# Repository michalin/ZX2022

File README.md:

# ZX 2022
Yet another homebuilt Z80 Computer, but this one works without any FPGAs or Microcontrollers, but components that were available at the time when the Z80 processor was state of the art. It can run historic CP/M programs like Multiplan, Wordstar and MBasic, as well as some games. This is a reminiscense to the Sinclair ZX81 computer. 
In contrast to its predecessor, the ZX2020, this one uses a 32 kilobyte EE Prom to reliably store the CP/M BDOS and BIOS. Furthermore a PS/2, or  PS/2 compatible USB keyboard can be connected. With an optional TMS99x8 based video card, a  TV or monitor can also be used. This repository contains gerber files for both the ZX2022 and the video  card. So it can now be easily replicated.

## Features
- Zilog Z80 processor @6MHz, higher clock rates might also work.
- 128 Kilobytes of static RAM, can be switched in banks of 32k
- 32 Kilobytes of EEprom
- 2 Serial UART ports 187.5 kBaud (Clock freqency/32):
  - Terminal emulation, (Putty works best)
  - File transfer. Files in a special folder on the PC show up as drive B>
- EEprom provides 15 Kilobytes of file memory (drive A>). CP/M executables are started automatically after reset or power on
- IDE (PATA) interface. Provides 4x16 Kilobyte organized as drives C>..F>
- CP/M 3.0
- 64-Pin connector for up to 6 Extension modules
- Optional graphics card with TMS99x8. 
    - 256x192 pixels and 15 colors
    - 32 Sprites (8x8, 16x16 or 32x32 upscaled)
    - NTSC (TMS9918) or PAL (TMS9928)
- Supports PS/2 or PS/2 compatible USB keyboards. New USB keyboards or wireless keyboards may NOT work.
- Now programmable in C using SDCC (Small Device C Compiler)

## To build the ZX 2022, do the following
- Wire the parts on a breadboard or prototype board according to the schematic. 
- OR: Make or order a PCB based on the gerber files `./Schematic/Mainboard/gerber-main.zip` (Recommended)
- Load the Arduino Sketch `loader/loader.ino` into an Arduino Mega
- Plug the Arduino Mega on the Bus connector, where it is marked on the silkscreen
- Connect the TxB and RxB pins of the DART with Pin 0 (TX0) and 1 (RX0) of your Arduino Mega
- Start a serial terminal emulation, for example "Putty", set 187500 Baud, 8 Bit, 1 Stopbit, no parity
- On Windows, run the tool `bin/loader.exe`. Click on "ROM Image" and select the file `CPM/rom.img`
- When a welcome message and the CP/M prompt "B>" appears on your terminal emulation, the ZX2020 is ready to use. If you have a PATA compatible hard drive connected, you need to format it under CP/M with the "mkdsk.com" tool before you can use it. Note that all data on the disk will be lost. 

## Using The Serial Disk Drive
Connect RX0 of the Arduino with TxB and TX0 with RxB of the ZX2022. 
It is not necessary to plug the Arduino into the pin header. Instead of an Arduino, a USB to serial converter may be used here as well. Select the serial port in the drop down menu and check the "Connect" check box to establish the serial connection. After a reset, the serial disk drive can be accessed as drive B>.

The folder [CPM/serdisk](./CPM/serdisk/) contains the CP/M programs in up to 16 user folders numbered from 0 to 15. If any of these files have changed, click the "Reload" Button to apply the changes. To access the files from CP/M, type `B`, followed by the user number 1-15 and a colon. For example `B5:` gives access to the files under [CPM/serdisk/5](./CPM/serdisk/5)

## Connecting a Hard Drive
IDE (PATA) hard drives can be connected through a 40-Pin connector. I recommend using a CompactFlash with a CF to IDE adapter. Best suitable are adapters that support power supply over pin 20 like this one: [https://amzn.to/3SFdIag](https://amzn.to/3SFdIag). call ´mkdsk.com´ on the serial disk drive B> to format the drive.

## The Autostart Feature
Clicking the `File` button in the loader app uploads an executable CP/M file (*.com) that is executed after each power-on or reboot. The loader app detects when there is a new version of this "autostart program" and restarts the ZX2022 with this new version. This function is particularly useful for writing new software.

## Connecting a PS/2 Keyboard
Connect a PS/2 Keyboard like shown below:

## Connecting a USB Keyboard
USB Keyboards can also be connected if they support the PS/2 protocol. Most older keyboards do so, but newer or wireless keyboards often don't. These will not work.
I recommend to make an adapter cable from an USB extension cable as shown below:

## Changing the keyboard layout 
This is only necessary with PS/2 or USB keyboards. With terminal connections, the settings of the Windows-OS apply.
To change the keyboard layout, set the `KBLAYOUT` variable in the file [CPM/SYSCFG.LIB](./CPM/SYSCFG.LIB) either to `DE` or `EN` (default)
and [rebuild the CP/M rom image](CPM/README.md).

## Using With the TMS9918 Video Card
You find the schematic and gerber files in [Schematic/Video/](./Schematic/Video/). Set a jumper or solder a bridge at the position `IO2` on the pin header J3. This configures the card for IO addresses starting at 20h. This setting must match the `p$vdp` constant in [CPM/SYSCFG.LIB](./CPM/SYSCFG.LIB)

The TMS9918 can only display 40 columns, while terminals display 80 columns. This CP/M version is built for 80 columns, but it can be changed to 40 columns. To do this, open the file [gencpm.dat](./CPM/gencpm.dat), change the constant `PAGWID` to 28 (Which is 40 in hex) and [rebuild the CP/M rom image](CPM/README.md).

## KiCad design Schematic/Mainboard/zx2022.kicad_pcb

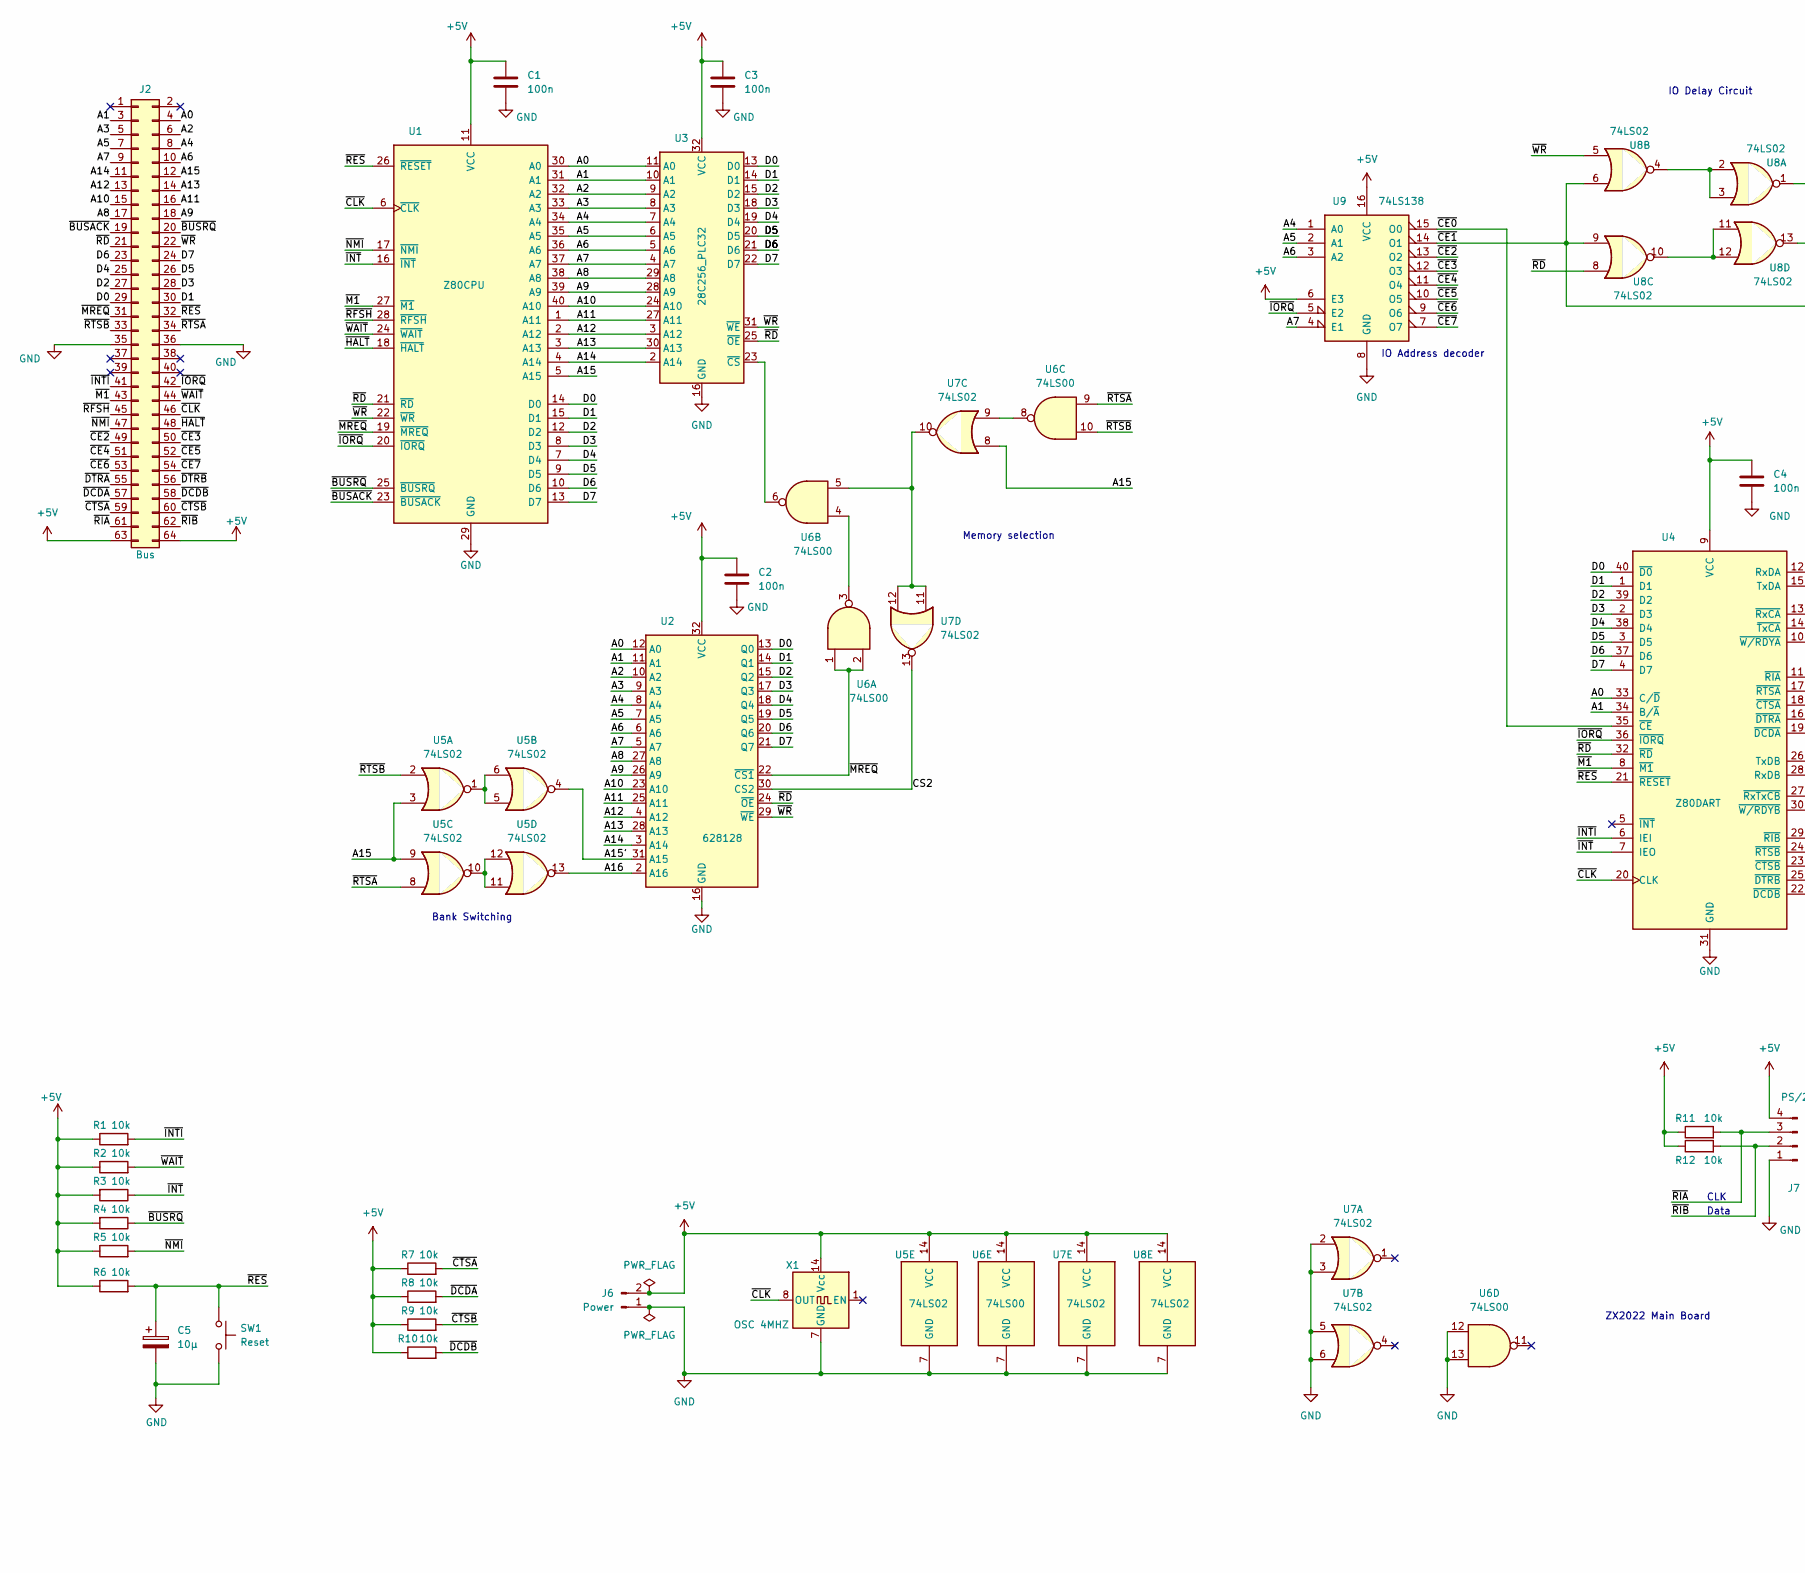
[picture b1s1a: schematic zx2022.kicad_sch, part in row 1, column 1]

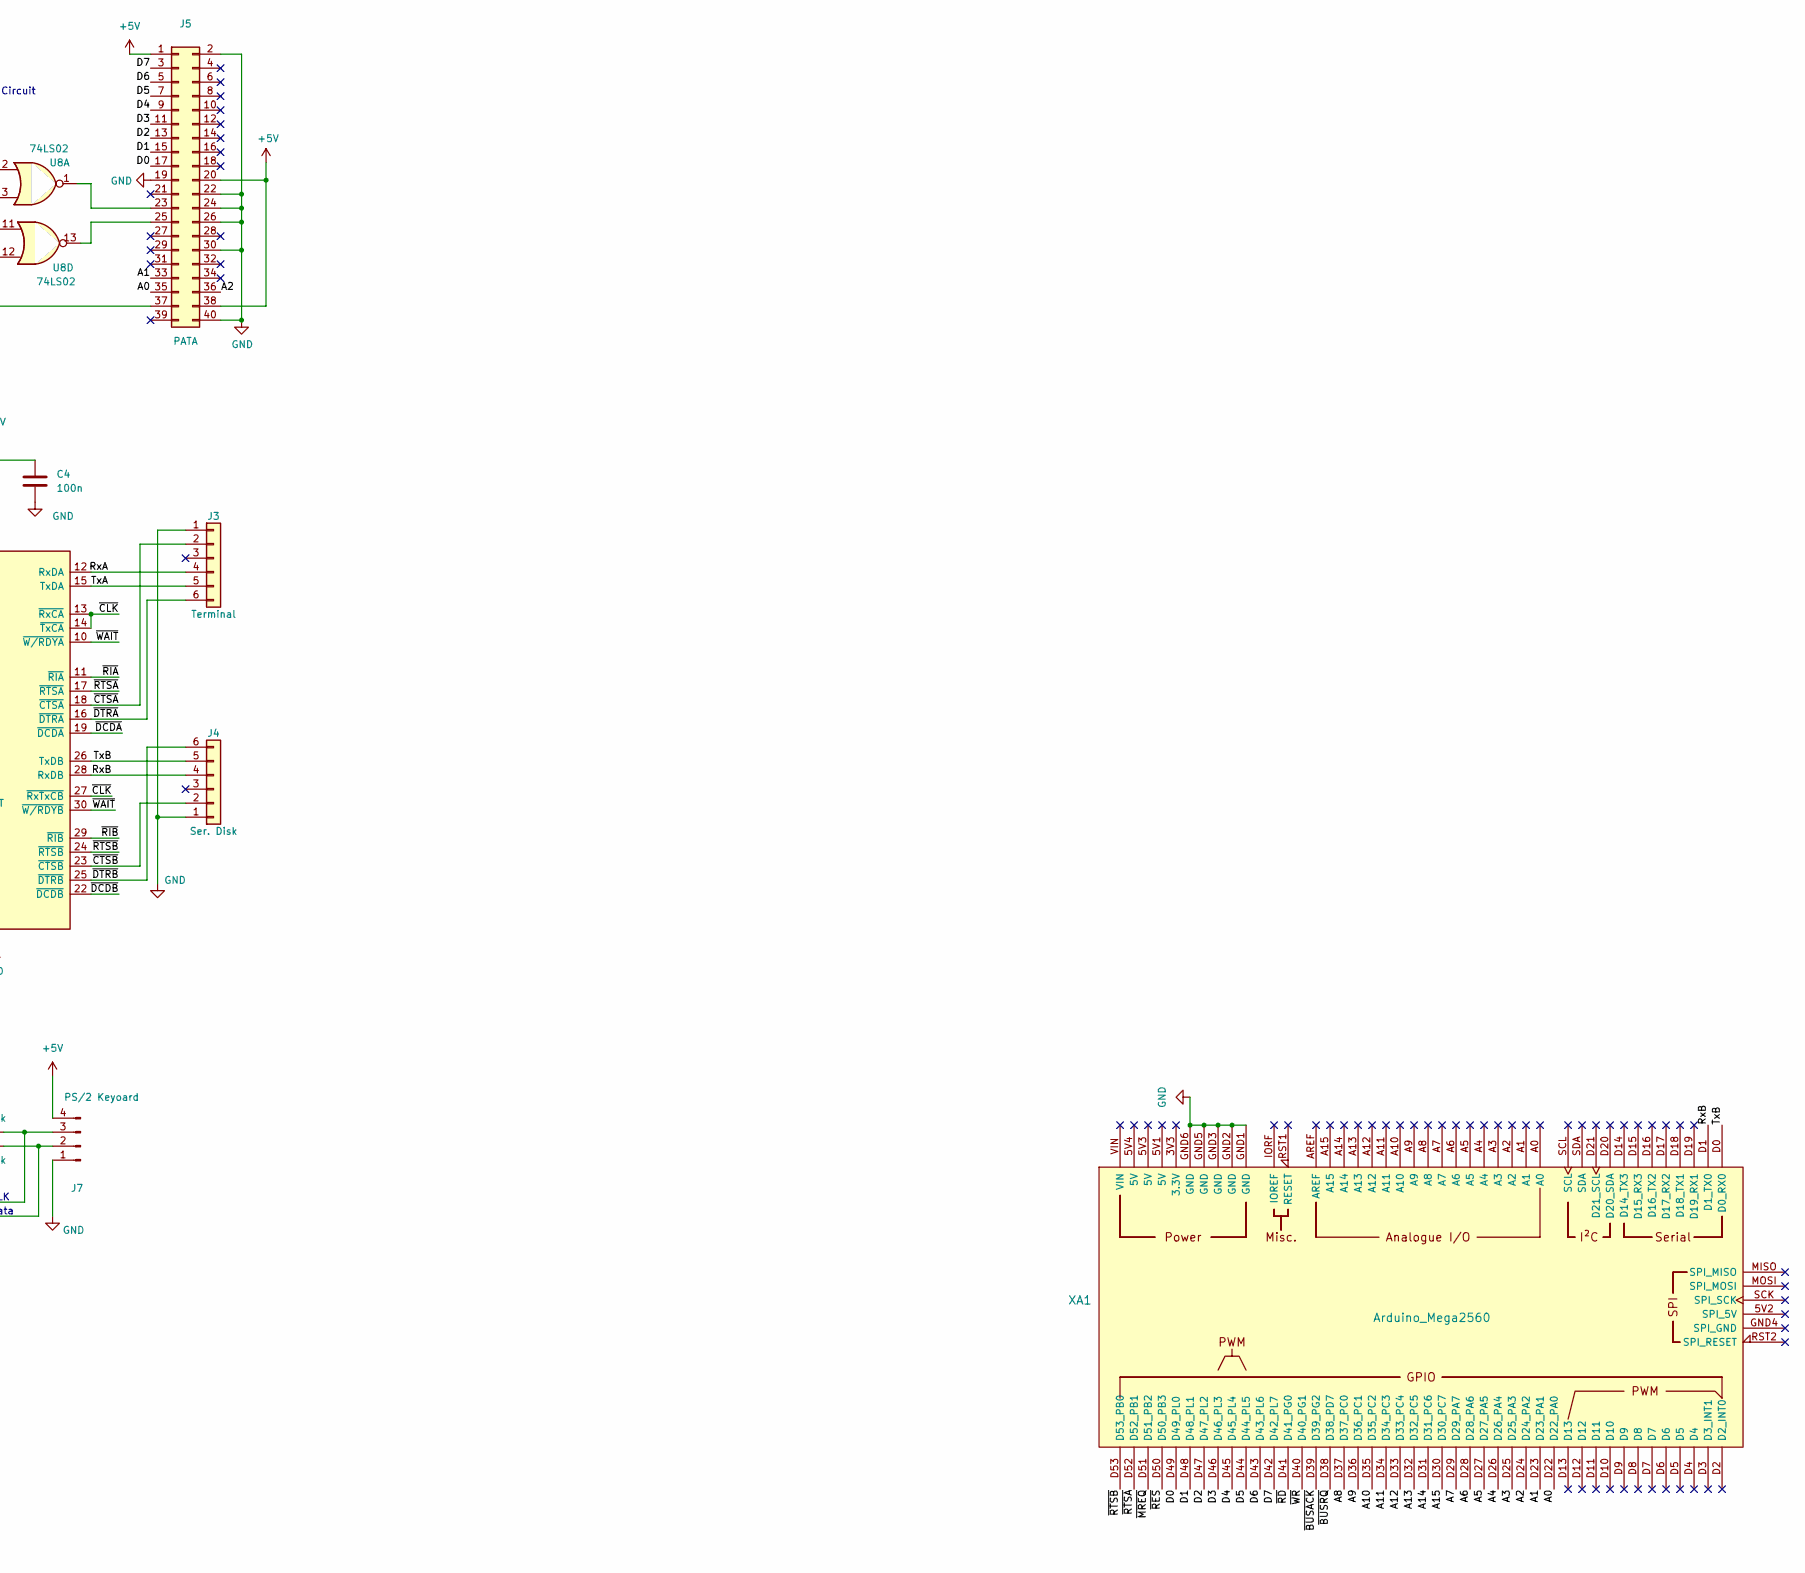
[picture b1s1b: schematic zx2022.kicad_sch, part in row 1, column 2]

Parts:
C1, C2, C3, C4: 100n; C_Disc_D5.0mm_W2.5mm_P2.50mm
C5: 10µ; CP_Radial_D5.0mm_P2.50mm
J2: Bus; PinHeader_2x32_P2.54mm_Vertical
J3: Terminal; PinSocket_1x06_P2.54mm_Vertical
J4: Ser. Disk; PinSocket_1x06_P2.54mm_Vertical
J5: PATA; BoxConn_2x20_P2.54mm_Horizontal
J6: Power; PinHeader_1x02_P2.54mm_Horizontal
J7: PS/2 Keyoard; PinHeader_1x04_P2.54mm_Horizontal
R1, R2, R3, R4, R5, R6, R7, R8, R9, R10, R11, R12: 10k; R_Axial_DIN0207_L6.3mm_D2.5mm_P7.62mm_Horizontal
SW1: Reset; SW_PUSH_6mm
U1: Z80CPU; DIP-40_W15.24mm_Socket
U2: 628128; DIP-32_W15.24mm_Socket
U3: 28C256_PLC32; PLCC-32_THT-Socket
U4: Z80DART; DIP-40_W15.24mm_Socket
U5, U7, U8: 74LS02; DIP-14_W7.62mm_Socket
U6: 74LS00; DIP-14_W7.62mm_Socket
U9: 74LS138; DIP-16_W7.62mm_Socket
X1: OSC 4MHZ; Oscillator_DIP-14
XA1: Arduino_Mega2560; Arduino_Mega2560_Shield

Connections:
+5V: C1.1, C2.1, C3.1, C4.1, J2.63, J2.64, J5.1, J5.20, J5.38, J6.2, J7.4, R1.1, R2.1, R3.2, R4.2, R5.1, R6.1, R7.1, R8.1, R9.1, R10.1, R11.1, R12.1, U1.11 (VCC), U2.32 (VCC), U3.32 (VCC), U4.9 (VCC), U5.14 (VCC), U6.14 (VCC), U7.14 (VCC), U8.14 (VCC), U9.6 (E3), U9.16 (VCC), X1.14 (Vcc)
/A0: J2.4, J5.35, U1.30 (A0), U2.12 (A0), U3.11 (A0), U4.33 (C/~D), XA1.D22 (D22_PA0)
/A1: J2.3, J5.33, U1.31 (A1), U2.11 (A1), U3.10 (A1), U4.34 (B/~A), XA1.D23 (D23_PA1)
/A2: J2.6, J5.36, U1.32 (A2), U2.10 (A2), U3.9 (A2), XA1.D24 (D24_PA2)
/A3: J2.5, U1.33 (A3), U2.9 (A3), U3.8 (A3), XA1.D25 (D25_PA3)
/A4: J2.8, U1.34 (A4), U2.8 (A4), U3.7 (A4), U9.1 (A0), XA1.D26 (D26_PA4)
/A5: J2.7, U1.35 (A5), U2.7 (A5), U3.6 (A5), U9.2 (A1), XA1.D27 (D27_PA5)
/A6: J2.10, U1.36 (A6), U2.6 (A6), U3.5 (A6), U9.3 (A2), XA1.D28 (D28_PA6)
/A7: J2.9, U1.37 (A7), U2.5 (A7), U3.4 (A7), U9.4 (E1), XA1.D29 (D29_PA7)
/A8: J2.17, U1.38 (A8), U2.27 (A8), U3.29 (A8), XA1.D37 (D37_PC0)
/A9: J2.18, U1.39 (A9), U2.26 (A9), U3.28 (A9), XA1.D36 (D36_PC1)
/A10: J2.15, U1.40 (A10), U2.23 (A10), U3.24 (A10), XA1.D35 (D35_PC2)
/A11: J2.16, U1.1 (A11), U2.25 (A11), U3.27 (A11), XA1.D34 (D34_PC3)
/A12: J2.13, U1.2 (A12), U2.4 (A12), U3.3 (A12), XA1.D33 (D33_PC4)
/A13: J2.14, U1.3 (A13), U2.28 (A13), U3.30 (A13), XA1.D32 (D32_PC5)
/A14: J2.11, U1.4 (A14), U2.3 (A14), U3.2 (A14), XA1.D31 (D31_PC6)
/A15: J2.12, U1.5 (A15), U5.3, U5.9, U7.8, XA1.D30 (D30_PC7)
/A15': U2.31 (A15), U5.4
/A16: U2.2 (A16), U5.13
/CS2: U2.30 (CS2), U7.13
/D0: J2.29, J5.17, U1.14 (D0), U2.13 (Q0), U3.13 (D0), U4.40 (~D0), XA1.D49 (D49_PL0)
/D1: J2.30, J5.15, U1.15 (D1), U2.14 (Q1), U3.14 (D1), U4.1 (D1), XA1.D48 (D48_PL1)
/D2: J2.27, J5.13, U1.12 (D2), U2.15 (Q2), U3.15 (D2), U4.39 (D2), XA1.D47 (D47_PL2)
/D3: J2.28, J5.11, U1.8 (D3), U2.17 (Q3), U3.18 (D3), U4.2 (D3), XA1.D46 (D46_PL3)
/D4: J2.25, J5.9, U1.7 (D4), U2.18 (Q4), U3.19 (D4), U4.38 (D4), XA1.D45 (D45_PL4)
/D5: J2.26, J5.7, U1.9 (D5), U2.19 (Q5), U3.20 (D5), U4.3 (D5), XA1.D44 (D44_PL5)
/D6: J2.23, J5.5, U1.10 (D6), U2.20 (Q6), U3.21 (D6), U4.37 (D6), XA1.D43 (D43_PL6)
/D7: J2.24, J5.3, U1.13 (D7), U2.21 (Q7), U3.22 (D7), U4.4 (D7), XA1.D42 (D42_PL7)
/RxA: J3.4, U4.12 (RxDA)
/RxB: J4.4, U4.28 (RxDB), XA1.D1 (D1_TX0)
/TxA: J3.5, U4.15 (TxDA)
/TxB: J4.5, U4.26 (TxDB), XA1.D0 (D0_RX0)
/~BUSACK: J2.19, U1.23 (~BUSACK), XA1.D39 (D39_PG2)
/~BUSRQ: J2.20, R4.1, U1.25 (~BUSRQ), XA1.D38 (D38_PD7)
/~CE0: U4.35 (~CE), U9.15 (O0)
/~CE1: J5.37, U8.6, U8.9, U9.14 (O1)
/~CE2: J2.49, U9.13 (O2)
/~CE3: J2.50, U9.12 (O3)
/~CE4: J2.51, U9.11 (O4)
/~CE5: J2.52, U9.10 (O5)
/~CE6: J2.53, U9.9 (O6)
/~CE7: J2.54, U9.7 (O7)
/~CLK: J2.46, U1.6 (~CLK), U4.13 (~RxCA), U4.14 (~TxCA), U4.20 (CLK), U4.27 (~RxTxCB), X1.8 (OUT)
/~CTSA: J2.59, J3.2, R7.2, U4.18 (~CTSA)
/~CTSB: J2.60, J4.2, R9.2, U4.23 (~CTSB)
/~DCDA: J2.57, R8.2, U4.19 (~DCDA)
/~DCDB: J2.58, R10.2, U4.22 (~DCDB)
/~DTRA: J2.55, J3.6, U4.16 (~DTRA)
/~DTRB: J2.56, J4.6, U4.25 (~DTRB)
/~HALT: J2.48, U1.18 (~HALT)
/~INTI: J2.41, R1.2, U4.6 (IEI)
/~INT: R3.1, U1.16 (~INT), U4.7 (IEO)
/~IORQ: J2.42, U1.20 (~IORQ), U4.36 (~IORQ), U9.5 (E2)
/~M1: J2.43, U1.27 (~M1), U4.8 (~M1)
/~MREQ: J2.31, U1.19 (~MREQ), U2.22 (~CS1), U6.1, U6.2, XA1.D51 (D51_PB2)
/~NMI: J2.47, R5.2, U1.17 (~NMI)
/~RD: J2.21, U1.21 (~RD), U2.24 (~OE), U3.25 (~OE), U4.32 (~RD), U8.8, XA1.D41 (D41_PG0)
/~RES: C5.1, J2.32, R6.2, SW1.1, U1.26 (~RESET), U4.21 (~RESET), XA1.D50 (D50_PB3)
/~RFSH: J2.45, U1.28 (~RFSH)
/~RIA: J2.61, J7.3, R11.2, U4.11 (~RIA)
/~RIB: J2.62, J7.2, R12.2, U4.29 (~RIB)
/~RTSA: J2.34, U4.17 (~RTSA), U5.8, U6.9, XA1.D52 (D52_PB1)
/~RTSB: J2.33, U4.24 (~RTSB), U5.2, U6.10, XA1.D53 (D53_PB0)
/~WAIT: J2.44, R2.2, U1.24 (~WAIT), U4.10 (~W/RDYA), U4.30 (~W/RDYB)
/~WR: J2.22, U1.22 (~WR), U2.29 (~WE), U3.31 (~WE), U8.5, XA1.D40 (D40_PG1)
GND: C1.2, C2.2, C3.2, C4.2, C5.2, J2.35, J2.36, J3.1, J4.1, J5.2, J5.19, J5.22, J5.24, J5.26, J5.30, J5.40, J6.1, J7.1, SW1.2, U1.29 (GND), U2.16 (GND), U3.16 (GND), U4.31 (GND), U5.7 (GND), U6.7 (GND), U6.12, U6.13, U7.2, U7.3, U7.5, U7.6, U7.7 (GND), U8.7 (GND), U9.8 (GND), X1.7 (GND), XA1.GND1 (GND), XA1.GND2 (GND), XA1.GND3 (GND), XA1.GND5 (GND), XA1.GND6 (GND)
unnamed: J5.23, U8.1
unnamed: J5.25, U8.13
unnamed: U3.23 (~CS), U6.6
unnamed: U5.1, U5.5, U5.6
unnamed: U5.10, U5.11, U5.12
unnamed: U6.3, U6.4
unnamed: U6.5, U7.10, U7.11, U7.12
unnamed: U6.8, U7.9
unnamed: U8.2, U8.3, U8.4
unnamed: U8.10, U8.11, U8.12

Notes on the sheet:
Bank Switching
IO Address decoder
CLK
ZX2022 Main Board
IO Delay Circuit
Memory selection
Data

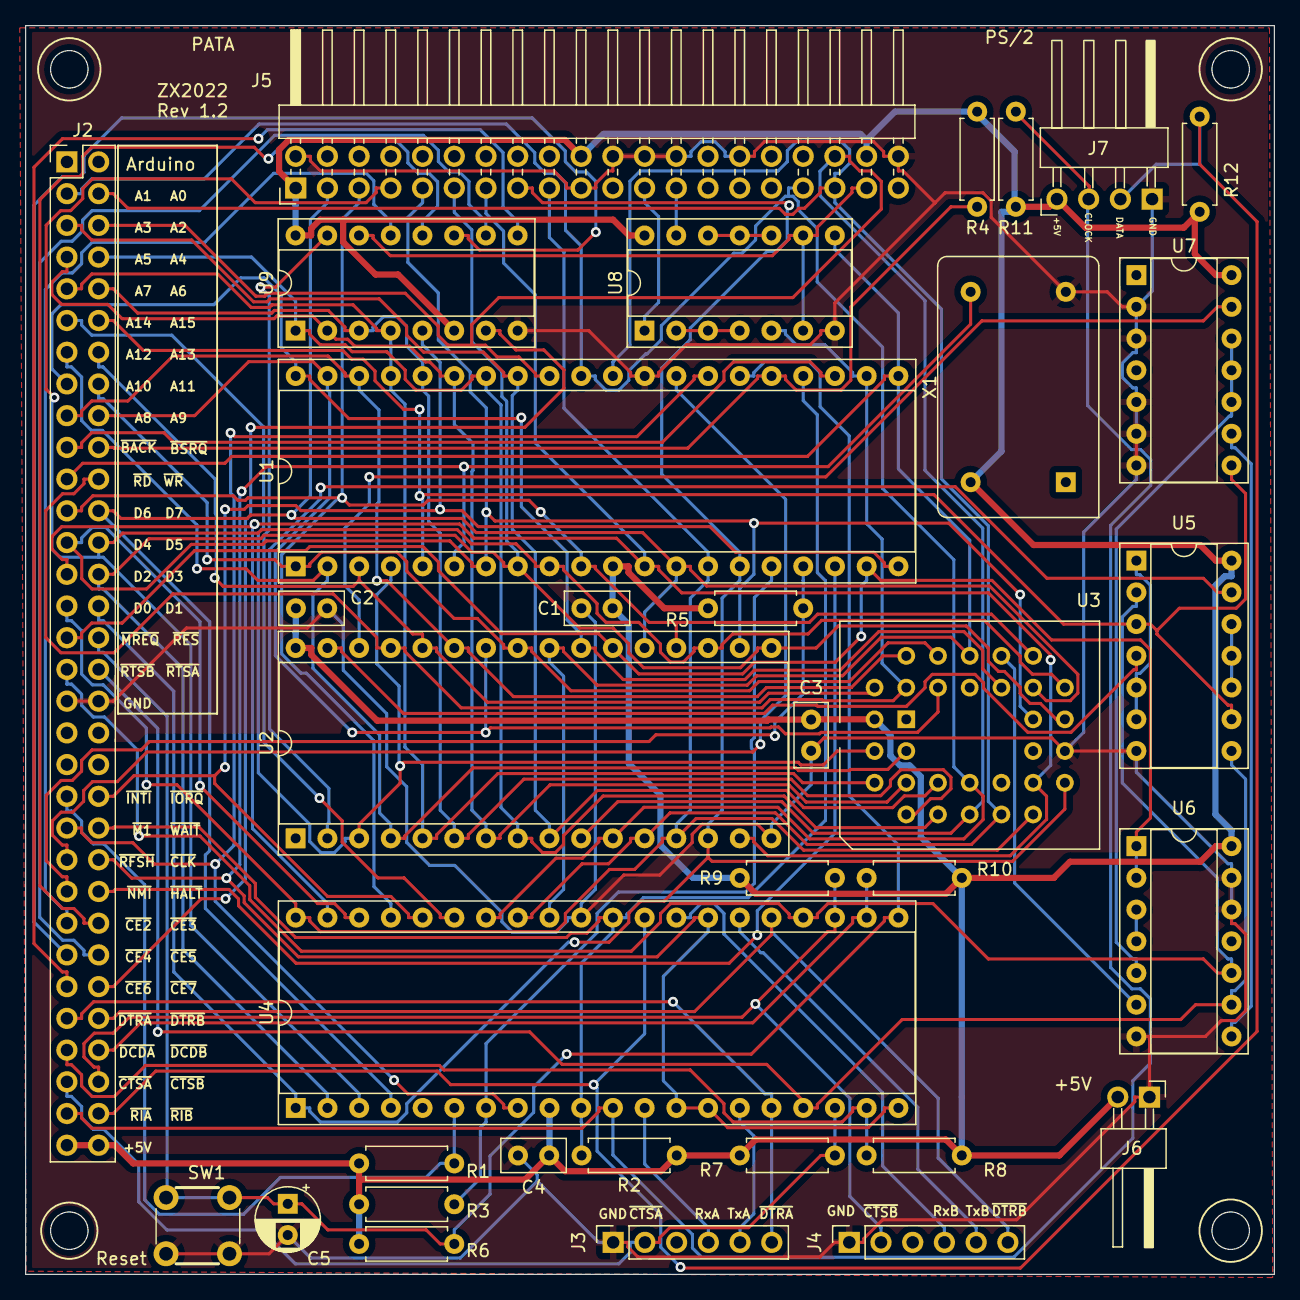
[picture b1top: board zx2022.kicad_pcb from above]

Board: 2 copper layers, 100.0 x 100.0 mm, 34 parts (0 on the bottom side), 76 nets.

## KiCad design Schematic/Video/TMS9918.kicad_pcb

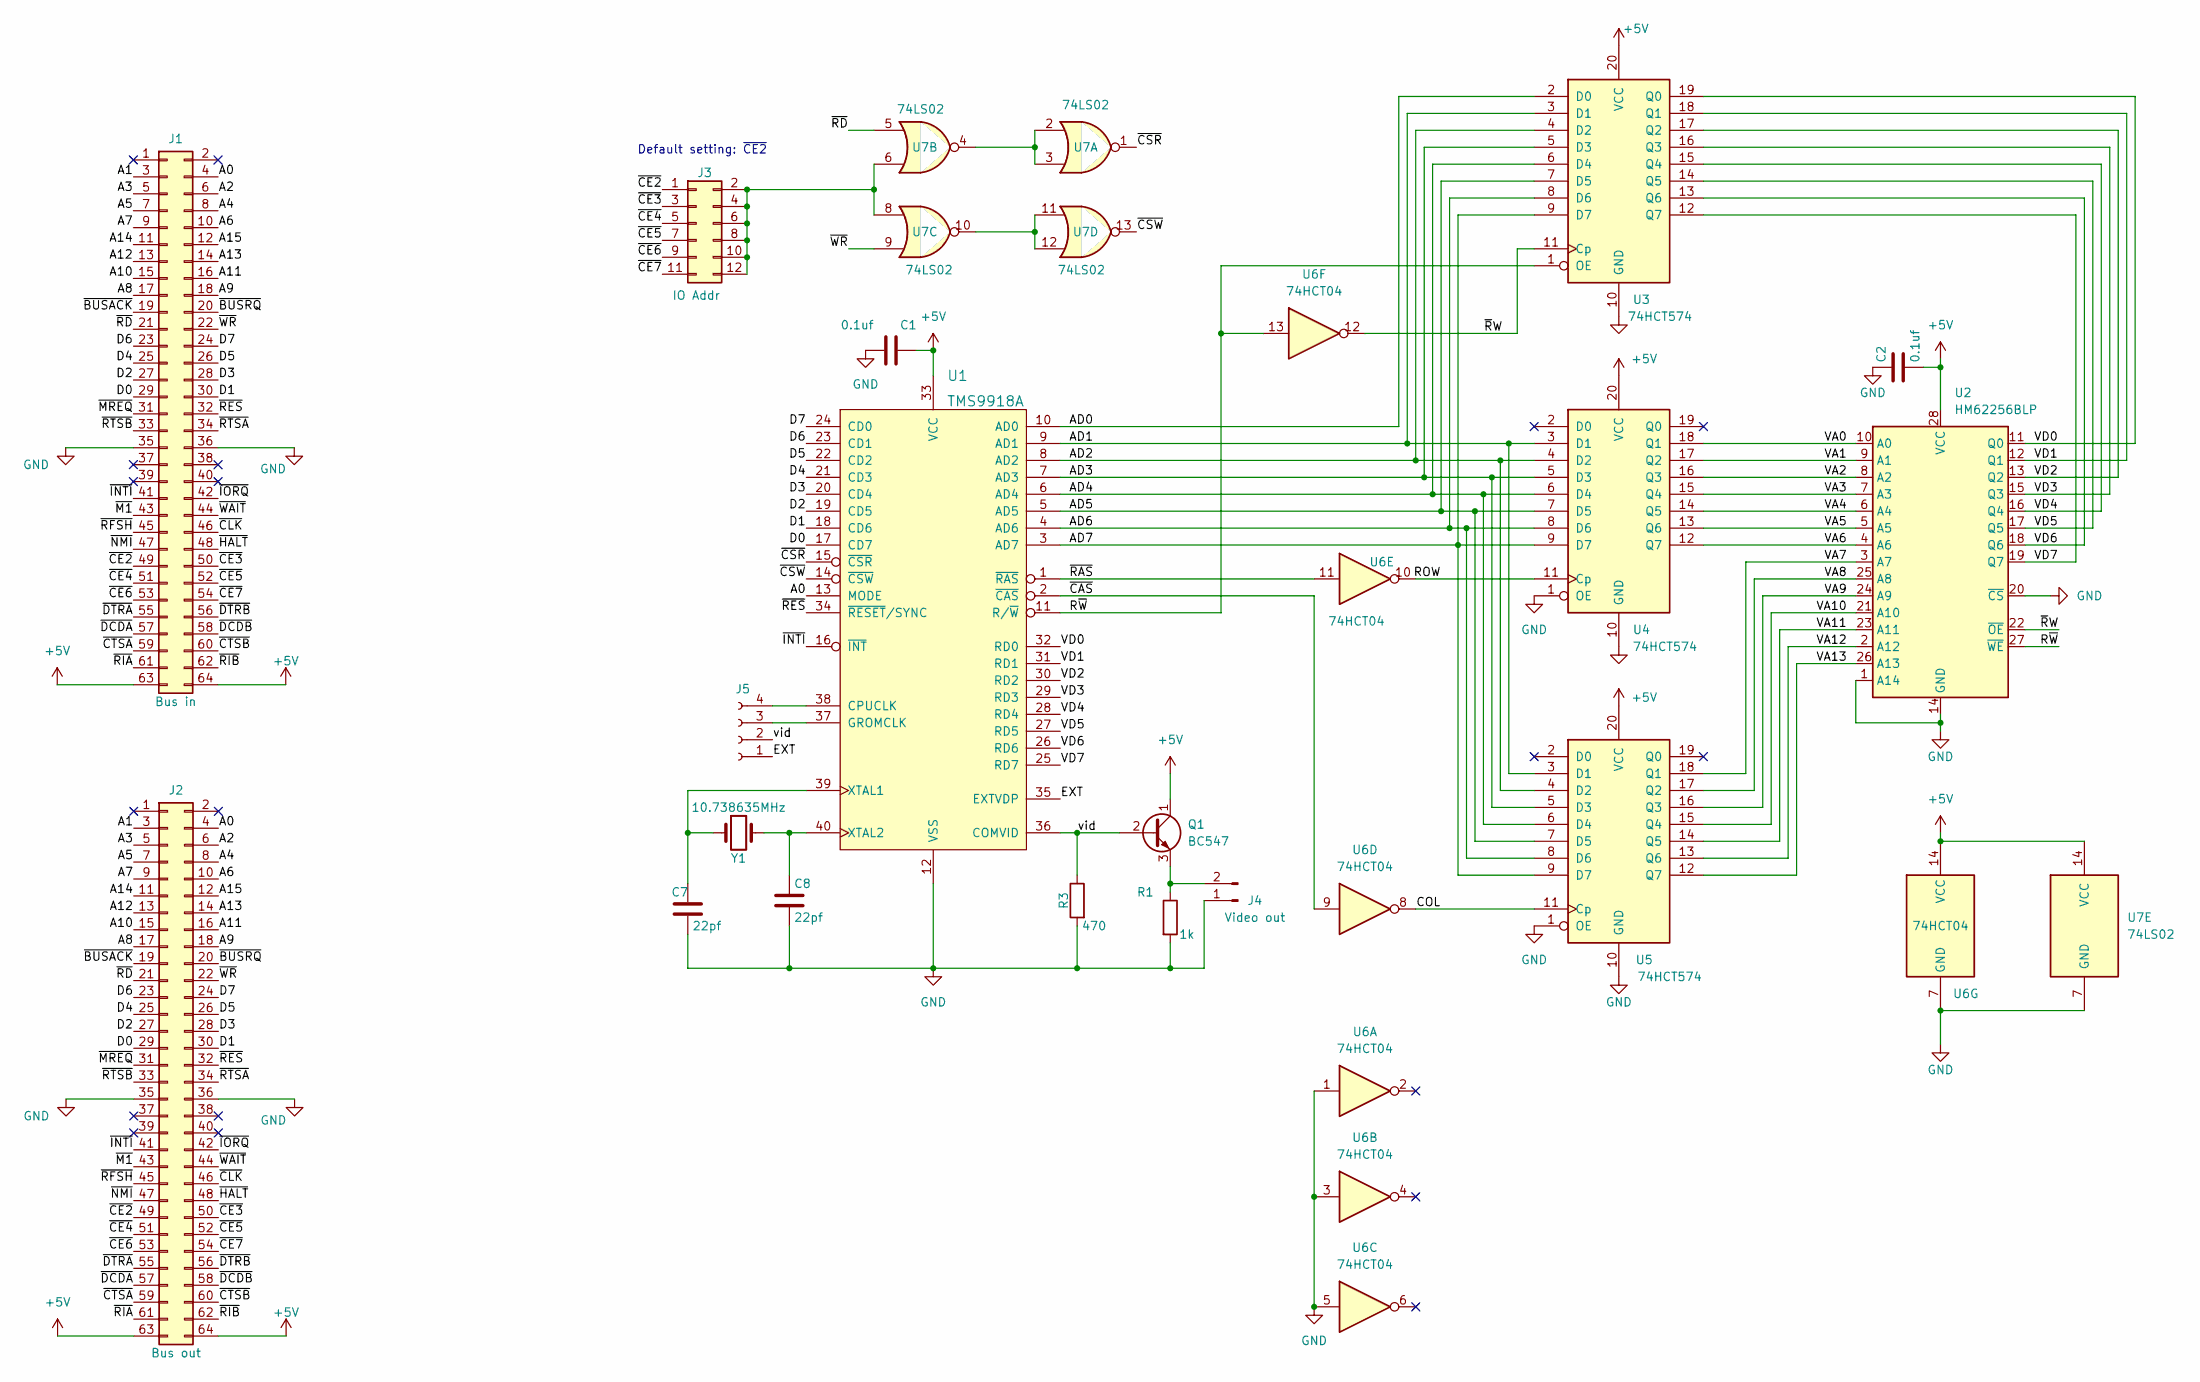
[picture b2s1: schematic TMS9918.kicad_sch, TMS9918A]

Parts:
C1, C2: 0.1uf; C_Disc_D3.0mm_W1.6mm_P2.50mm
C7, C8: 22pf; C_Disc_D3.0mm_W1.6mm_P2.50mm
J1: Bus in; PinHeader_2x32_P2.54mm_Vertical
J2: Bus out; PinHeader_2x32_P2.54mm_Vertical
J3: IO Addr; PinHeader_2x06_P2.54mm_Vertical
J4: Video out; PinHeader_1x02_P2.54mm_Horizontal
J5: Conn_01x04_Female; PinHeader_1x04_P2.54mm_Vertical
Q1: BC547; TO-92_Inline
R1: 1k; R_Axial_DIN0207_L6.3mm_D2.5mm_P7.62mm_Horizontal
R3: 470; R_Axial_DIN0207_L6.3mm_D2.5mm_P7.62mm_Horizontal
U1: TMS9918A; DIP-40_W15.24mm_Socket
U2: HM62256BLP; DIP-28_W15.24mm
U3, U4, U5: 74HCT574; DIP-20_W7.62mm_Socket
U6: 74HCT04; DIP-14_W7.62mm_Socket
U7: 74LS02; DIP-14_W7.62mm_Socket
Y1: 10.738635MHz; Crystal_HC49-4H_Vertical

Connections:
+5V: C1.1, C2.2, J1.63, J1.64, J2.63, J2.64, Q1.1 (C), U1.33 (VCC), U2.28 (VCC), U3.20 (VCC), U4.20 (VCC), U5.20 (VCC), U6.14 (VCC), U7.14 (VCC)
/A0: J1.4, J2.4, U1.13 (MODE)
/A1: J1.3, J2.3
/A2: J1.6, J2.6
/A3: J1.5, J2.5
/A4: J1.8, J2.8
/A5: J1.7, J2.7
/A6: J1.10, J2.10
/A7: J1.9, J2.9
/A8: J1.17, J2.17
/A9: J1.18, J2.18
/A10: J1.15, J2.15
/A11: J1.16, J2.16
/A12: J1.13, J2.13
/A13: J1.14, J2.14
/A14: J1.11, J2.11
/A15: J1.12, J2.12
/AD0: U1.10 (AD0), U3.2 (D0)
/AD1: U1.9 (AD1), U3.3 (D1), U4.3 (D1), U5.3 (D1)
/AD2: U1.8 (AD2), U3.4 (D2), U4.4 (D2), U5.4 (D2)
/AD3: U1.7 (AD3), U3.5 (D3), U4.5 (D3), U5.5 (D3)
/AD4: U1.6 (AD4), U3.6 (D4), U4.6 (D4), U5.6 (D4)
/AD5: U1.5 (AD5), U3.7 (D5), U4.7 (D5), U5.7 (D5)
/AD6: U1.4 (AD6), U3.8 (D6), U4.8 (D6), U5.8 (D6)
/AD7: U1.3 (AD7), U3.9 (D7), U4.9 (D7), U5.9 (D7)
/COL: U5.11 (Cp), U6.8
/D0: J1.29, J2.29, U1.17 (CD7)
/D1: J1.30, J2.30, U1.18 (CD6)
/D2: J1.27, J2.27, U1.19 (CD5)
/D3: J1.28, J2.28, U1.20 (CD4)
/D4: J1.25, J2.25, U1.21 (CD3)
/D5: J1.26, J2.26, U1.22 (CD2)
/D6: J1.23, J2.23, U1.23 (CD1)
/D7: J1.24, J2.24, U1.24 (CD0)
/EXT: J5.1, U1.35 (EXTVDP)
/ROW: U4.11 (Cp), U6.10
/R~W: U1.11 (R/~W), U2.27 (~WE), U3.1 (OE), U6.13
/VA0: U2.10 (A0), U4.18 (Q1)
/VA1: U2.9 (A1), U4.17 (Q2)
/VA2: U2.8 (A2), U4.16 (Q3)
/VA3: U2.7 (A3), U4.15 (Q4)
/VA4: U2.6 (A4), U4.14 (Q5)
/VA5: U2.5 (A5), U4.13 (Q6)
/VA6: U2.4 (A6), U4.12 (Q7)
/VA7: U2.3 (A7), U5.18 (Q1)
/VA8: U2.25 (A8), U5.17 (Q2)
/VA9: U2.24 (A9), U5.16 (Q3)
/VA10: U2.21 (A10), U5.15 (Q4)
/VA11: U2.23 (A11), U5.14 (Q5)
/VA12: U2.2 (A12), U5.13 (Q6)
/VA13: U2.26 (A13), U5.12 (Q7)
/VD0: U1.32 (RD0), U2.11 (Q0), U3.19 (Q0)
/VD1: U1.31 (RD1), U2.12 (Q1), U3.18 (Q1)
/VD2: U1.30 (RD2), U2.13 (Q2), U3.17 (Q2)
/VD3: U1.29 (RD3), U2.15 (Q3), U3.16 (Q3)
/VD4: U1.28 (RD4), U2.16 (Q4), U3.15 (Q4)
/VD5: U1.27 (RD5), U2.17 (Q5), U3.14 (Q5)
/VD6: U1.26 (RD6), U2.18 (Q6), U3.13 (Q6)
/VD7: U1.25 (RD7), U2.19 (Q7), U3.12 (Q7)
/vid: J5.2, Q1.2 (B), R3.1, U1.36 (COMVID)
/~BUSACK: J1.19, J2.19
/~BUSRQ: J1.20, J2.20
/~CAS: U1.2 (~CAS), U6.9
/~CE2: J1.49, J2.49, J3.1
/~CE3: J1.50, J2.50, J3.3
/~CE4: J1.51, J2.51, J3.5
/~CE5: J1.52, J2.52, J3.7
/~CE6: J1.53, J2.53, J3.9
/~CE7: J1.54, J2.54, J3.11
/~CLK: J1.46, J2.46
/~CSR: U1.15 (~CSR), U7.1
/~CSW: U1.14 (~CSW), U7.13
/~CTSA: J1.59, J2.59
/~CTSB: J1.60, J2.60
/~DCDA: J1.57, J2.57
/~DCDB: J1.58, J2.58
/~DTRA: J1.55, J2.55
/~DTRB: J1.56, J2.56
/~HALT: J1.48, J2.48
/~INTI: J1.41, J2.41, U1.16 (~INT)
/~IORQ: J1.42, J2.42
/~M1: J1.43, J2.43
/~MREQ: J1.31, J2.31
/~NMI: J1.47, J2.47
/~RAS: U1.1 (~RAS), U6.11
/~RD: J1.21, J2.21, U7.5
/~RES: J1.32, J2.32, U1.34 (~RESET/SYNC)
/~RFSH: J1.45, J2.45
/~RIA: J1.61, J2.61
/~RIB: J1.62, J2.62
/~RTSA: J1.34, J2.34
/~RTSB: J1.33, J2.33
/~RW: U2.22 (~OE), U3.11 (Cp), U6.12
/~WAIT: J1.44, J2.44
/~WR: J1.22, J2.22, U7.9
GND: C1.2, C2.1, C7.2, C8.2, J1.35, J1.36, J2.35, J2.36, J4.1, R1.2, R3.2, U1.12 (VSS), U2.1 (A14), U2.14 (GND), U2.20 (~CS), U3.10 (GND), U4.1 (OE), U4.10 (GND), U5.1 (OE), U5.10 (GND), U6.1, U6.3, U6.5, U6.7 (GND), U7.7 (GND)
unnamed: C7.1, U1.39 (XTAL1), Y1.1
unnamed: C8.1, U1.40 (XTAL2), Y1.2
unnamed: J3.2, J3.4, J3.6, J3.8, J3.10, J3.12, U7.6, U7.8
unnamed: J4.2, Q1.3 (E), R1.1
unnamed: J5.4, U1.38 (CPUCLK)
unnamed: J5.3, U1.37 (GROMCLK)
unnamed: U7.2, U7.3, U7.4
unnamed: U7.10, U7.11, U7.12

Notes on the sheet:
Default setting: ~{CE2}

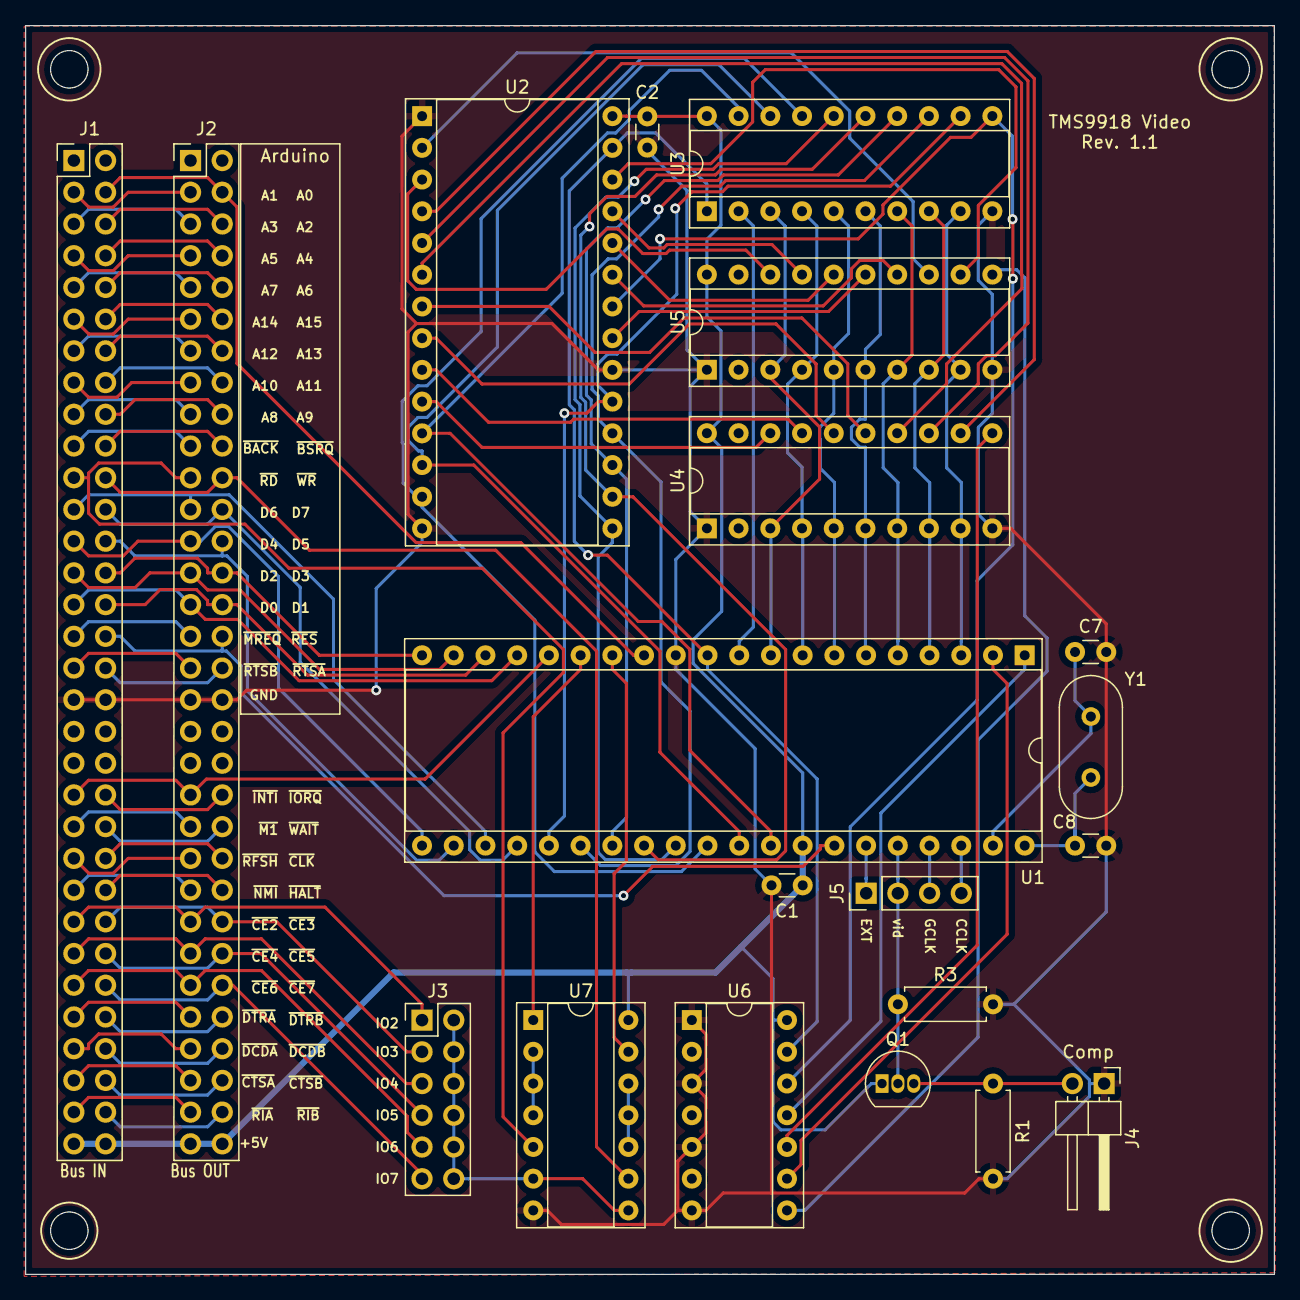
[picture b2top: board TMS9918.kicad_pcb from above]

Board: 2 copper layers, 100.0 x 100.0 mm, 20 parts (0 on the bottom side), 104 nets.

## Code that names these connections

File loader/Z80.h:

/* Copyright (C) 2020  Doctor Volt

 This program is free software: you can redistribute it and/or modify
 it under the terms of the GNU General Public License as published by
 the Free Software Foundation, either version 3 of the License, or
 (at your option) any later version.

 This program is distributed in the hope that it will be useful,
 but WITHOUT ANY WARRANTY; without even the implied warranty of
 MERCHANTABILITY or FITNESS FOR A PARTICULAR PURPOSE.  See the
 GNU General Public License for more details.

 You should have received a copy of the GNU General Public License
 along with this program.  If not, see <https://www.gnu.org/licenses/>.
*/

#ifndef Z80_H
#define Z80_H

#include <Arduino.h>
// Port B
#define RTSB_PIN PB0 //(Arduino Pin 53) 
#define RTSA_PIN PB1 //(Arduino Pin 52) 
#define MREQ_PIN PB2 //(Arduino Pin 51) Z80 Pin 19
#define RST_PIN PB3 //(Arduino Pin 50) Z80 PIN 26
// Port G
#define RD_PIN PG0   //(Arduino Pin 41) Z80 Pin 21
#define WR_PIN PG1   //(Arduino Pin 40) Z80 Pin 22
#define BUSACK_PIN PG2 //(Arduino Pin 39) Z80 Pin 23
// Port D
#define BUSRQ_PIN PD7  //(Artduino Pin 38) Z80 Pin 25
// Port E
#define TX0_PIN PE0 //(Arduino Pin0 / RX0)
#define TX1_PIN PE1 //(Arduino Pin1 / TX1)
// Address bus
#define ADDR_LO PINA // A0..A7
#define ADDR_HI PINC // A8..A9
#define ADDR ((ADDR_HI << 8) + ADDR_LO)

#define ACTIVE 1  // 0V
#define PASSIVE 0 // 5V, pulled up by 10k resistor

#define BUSERROR 0 //BUSACK failed

inline void RD(uint8_t b)
{
  (b == ACTIVE) ? bitClear(PORTG, RD_PIN) : bitSet(PORTG, RD_PIN);
}
inline void WR(uint8_t b)
{
  (b == ACTIVE) ? bitClear(PORTG, WR_PIN) : bitSet(PORTG, WR_PIN);
}

inline void MREQ(uint8_t b)
{
  (b == ACTIVE) ? bitClear(PORTB, MREQ_PIN) : bitSet(PORTB, MREQ_PIN);
}

inline void BUSALLOC(bool b)
{
  if (b) // Allocate bus
  {
    DDRA = 0xFF; //Addr LO
    DDRC = 0xFF; //Addr HI
    DDRL = 0xFF; //Data
    DDRB |= (1 << MREQ_PIN);
    PORTB |= (1 << MREQ_PIN); //All high (passive)
    DDRG |= (1 << RD_PIN) + (1 << WR_PIN);
    PORTG |= (1 << RD_PIN) + (1 << WR_PIN);
  }
  else // Free bus
  {
    DDRA = 0;
    DDRC = 0;
    DDRL = 0;
    DDRB &= ~((1 << MREQ_PIN) + (1 << RTSA_PIN) + (1 << RTSB_PIN));
    DDRG &= ~((1 << RD_PIN) + (1 << WR_PIN));
  }
}

inline bool BUSRQ(bool b)
{
  b ? bitSet(DDRD, BUSRQ_PIN) : bitClear(DDRD, BUSRQ_PIN);

  //Has Z80 ack'ed the request?
  delay(100);
  if (bitRead(PING, BUSACK_PIN) == b)
  {
    bitClear(DDRD, BUSRQ_PIN); 
    return BUSERROR;
  }

  BUSALLOC(b);
  return 1;
}

inline void RESET(bool b)
{
  b == ACTIVE ? bitSet(DDRB, RST_PIN) : bitClear(DDRB, RST_PIN);
}

inline void RESET()
{
  RESET(ACTIVE);
  delay(100);
  RESET(PASSIVE);
}

#endif

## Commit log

2022-10-01 Version 1.0
2023-02-12 Board version 1.2
2023-03-10 Version 1.1
    Bugfixes, SDCC integration
